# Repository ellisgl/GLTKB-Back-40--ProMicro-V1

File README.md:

# GLTKB Back 40% ProMicro V1
The other 40% mechanical keyboard.

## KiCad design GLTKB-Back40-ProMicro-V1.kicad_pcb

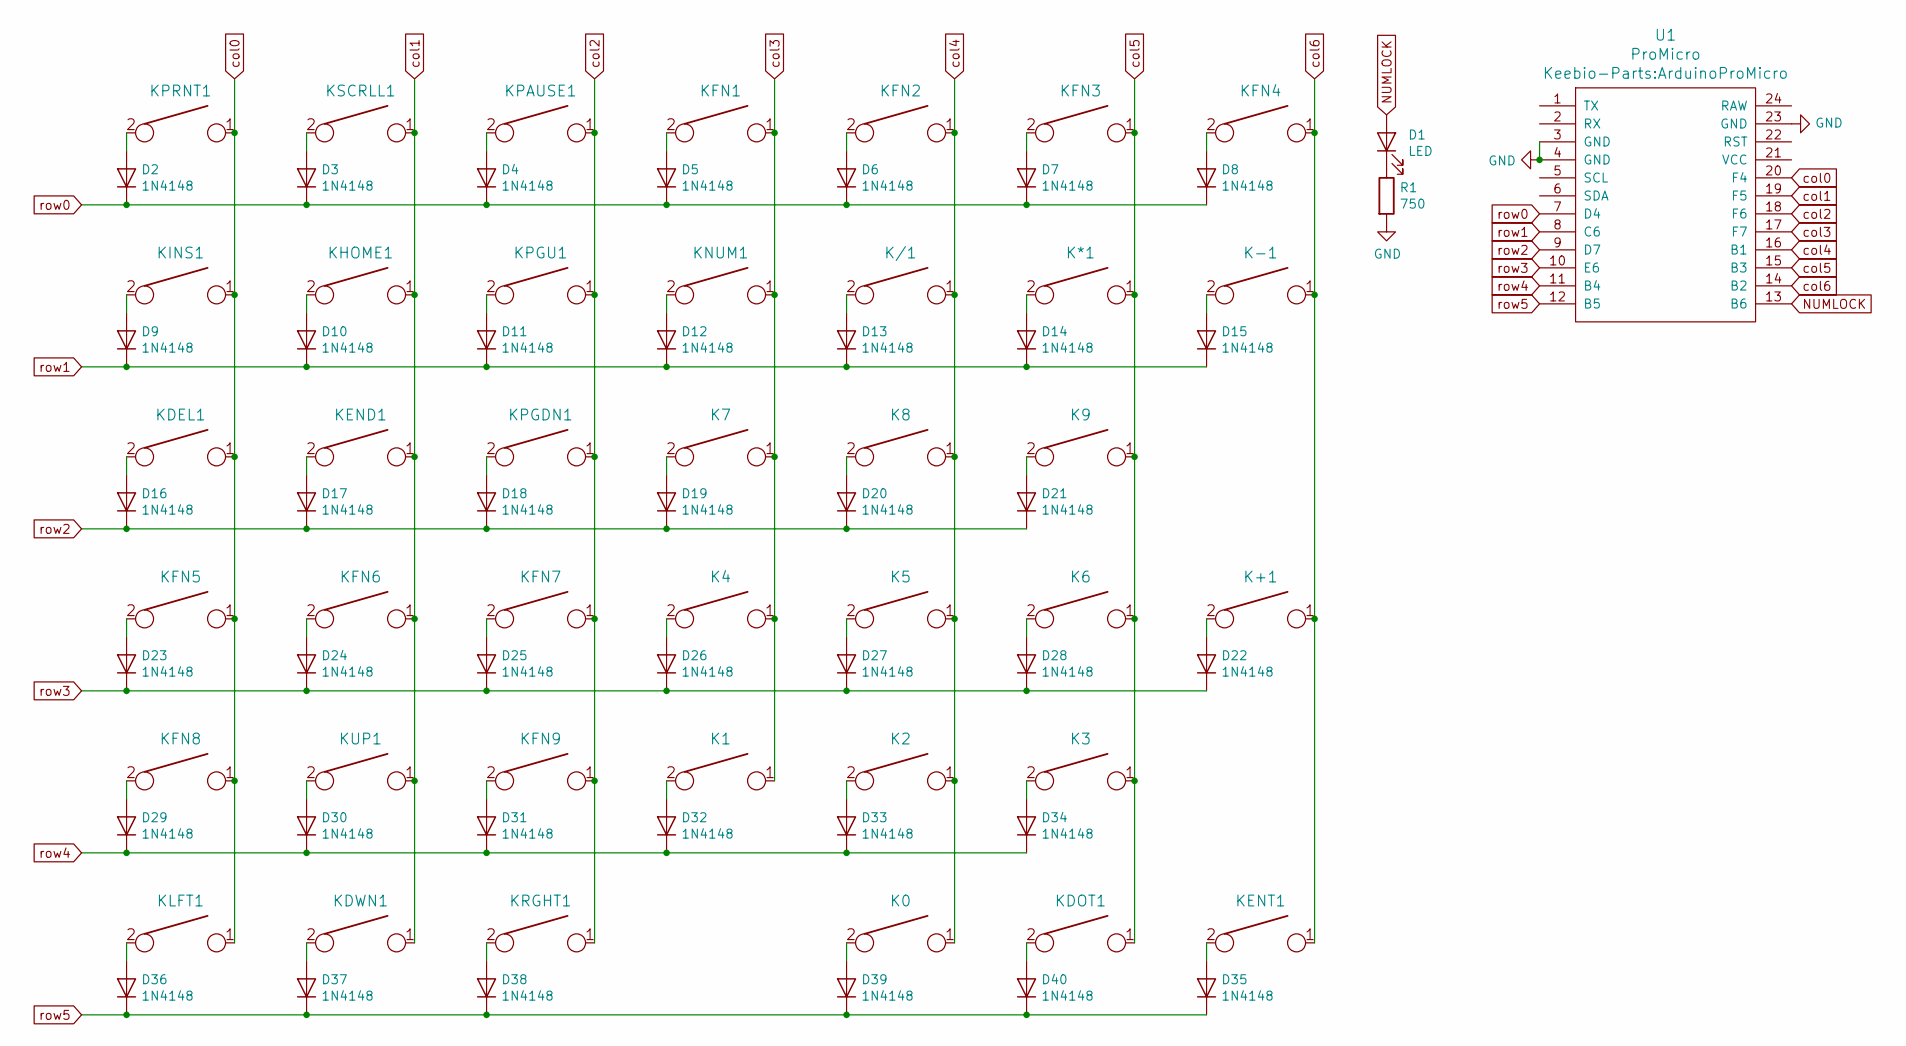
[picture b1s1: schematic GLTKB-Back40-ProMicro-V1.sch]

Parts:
D1: LED; LED_D3.0mm
D2, D3, D4, D5, D6, D7, D8, D9, D10, D11, D12, D13, D14, D15, D16, D17, D18, D19, D20, D21, D22, D23, D24, D25, D26, D27, D28, D29, D30, D31, D32, D33, D34, D35, D36, D37, D38, D39, D40: 1N4148; Diode-Hybrid-Back
K0, K1, K2, K3, K4, K5, K6, K7, K8, K9: KEYSW; Kailh_socket_MX
K*1: KEYSW; Kailh_socket_MX
K+1: KEYSW; Kailh_socket_MX
K-1: KEYSW; Kailh_socket_MX
K/1: KEYSW; Kailh_socket_MX
KDEL1: KEYSW; Kailh_socket_MX
KDOT1: KEYSW; Kailh_socket_MX
KDWN1: KEYSW; Kailh_socket_MX
KEND1: KEYSW; Kailh_socket_MX
KENT1: KEYSW; Kailh_socket_MX
KFN1, KFN2, KFN3, KFN4, KFN5, KFN6, KFN7, KFN8, KFN9: KEYSW; Kailh_socket_MX
KHOME1: KEYSW; Kailh_socket_MX
KINS1: KEYSW; Kailh_socket_MX
KLFT1: KEYSW; Kailh_socket_MX
KNUM1: KEYSW; Kailh_socket_MX
KPAUSE1: KEYSW; Kailh_socket_MX
KPGDN1: KEYSW; Kailh_socket_MX
KPGU1: KEYSW; Kailh_socket_MX
KPRNT1: KEYSW; Kailh_socket_MX
KRGHT1: KEYSW; Kailh_socket_MX
KSCRLL1: KEYSW; Kailh_socket_MX
KUP1: KEYSW; Kailh_socket_MX
R1: 750; R_Axial_DIN0207_L6.3mm_D2.5mm_P10.16mm_Horizontal
U1: ProMicro; ArduinoProMicro

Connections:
GND: R1.2, U1.3 (GND), U1.4 (GND), U1.23 (GND)
NUMLOCK: D1.2 (A), U1.13 (B6)
unnamed: D1.1 (K), R1.1
unnamed: D2.2 (A), KPRNT1.2
unnamed: D3.2 (A), KSCRLL1.2
unnamed: D4.2 (A), KPAUSE1.2
unnamed: D5.2 (A), KFN1.2
unnamed: D6.2 (A), KFN2.2
unnamed: D7.2 (A), KFN3.2
unnamed: D8.2 (A), KFN4.2
unnamed: D9.2 (A), KINS1.2
unnamed: D10.2 (A), KHOME1.2
unnamed: D11.2 (A), KPGU1.2
unnamed: D12.2 (A), KNUM1.2
unnamed: D13.2 (A), K/1.2
unnamed: D14.2 (A), K*1.2
unnamed: D15.2 (A), K-1.2
unnamed: D16.2 (A), KDEL1.2
unnamed: D17.2 (A), KEND1.2
unnamed: D18.2 (A), KPGDN1.2
unnamed: D19.2 (A), K7.2
unnamed: D20.2 (A), K8.2
unnamed: D21.2 (A), K9.2
unnamed: D22.2 (A), K+1.2
unnamed: D23.2 (A), KFN5.2
unnamed: D24.2 (A), KFN6.2
unnamed: D25.2 (A), KFN7.2
unnamed: D26.2 (A), K4.2
unnamed: D27.2 (A), K5.2
unnamed: D28.2 (A), K6.2
unnamed: D29.2 (A), KFN8.2
unnamed: D30.2 (A), KUP1.2
unnamed: D31.2 (A), KFN9.2
unnamed: D32.2 (A), K1.2
unnamed: D33.2 (A), K2.2
unnamed: D34.2 (A), K3.2
unnamed: D35.2 (A), KENT1.2
unnamed: D36.2 (A), KLFT1.2
unnamed: D37.2 (A), KDWN1.2
unnamed: D38.2 (A), KRGHT1.2
unnamed: D39.2 (A), K0.2
unnamed: D40.2 (A), KDOT1.2
col0: KDEL1.1, KFN5.1, KFN8.1, KINS1.1, KLFT1.1, KPRNT1.1, U1.20 (F4)
col1: KDWN1.1, KEND1.1, KFN6.1, KHOME1.1, KSCRLL1.1, KUP1.1, U1.19 (F5)
col2: KFN7.1, KFN9.1, KPAUSE1.1, KPGDN1.1, KPGU1.1, KRGHT1.1, U1.18 (F6)
col3: K1.1, K4.1, K7.1, KFN1.1, KNUM1.1, U1.17 (F7)
col4: K0.1, K2.1, K5.1, K8.1, K/1.1, KFN2.1, U1.16 (B1)
col5: K3.1, K6.1, K9.1, K*1.1, KDOT1.1, KFN3.1, U1.15 (B3)
col6: K+1.1, K-1.1, KENT1.1, KFN4.1, U1.14 (B2)
row0: D2.1 (K), D3.1 (K), D4.1 (K), D5.1 (K), D6.1 (K), D7.1 (K), D8.1 (K), U1.7 (D4)
row1: D9.1 (K), D10.1 (K), D11.1 (K), D12.1 (K), D13.1 (K), D14.1 (K), D15.1 (K), U1.8 (C6)
row2: D16.1 (K), D17.1 (K), D18.1 (K), D19.1 (K), D20.1 (K), D21.1 (K), U1.9 (D7)
row3: D22.1 (K), D23.1 (K), D24.1 (K), D25.1 (K), D26.1 (K), D27.1 (K), D28.1 (K), U1.10 (E6)
row4: D29.1 (K), D30.1 (K), D31.1 (K), D32.1 (K), D33.1 (K), D34.1 (K), U1.11 (B4)
row5: D35.1 (K), D36.1 (K), D37.1 (K), D38.1 (K), D39.1 (K), D40.1 (K), U1.12 (B5)

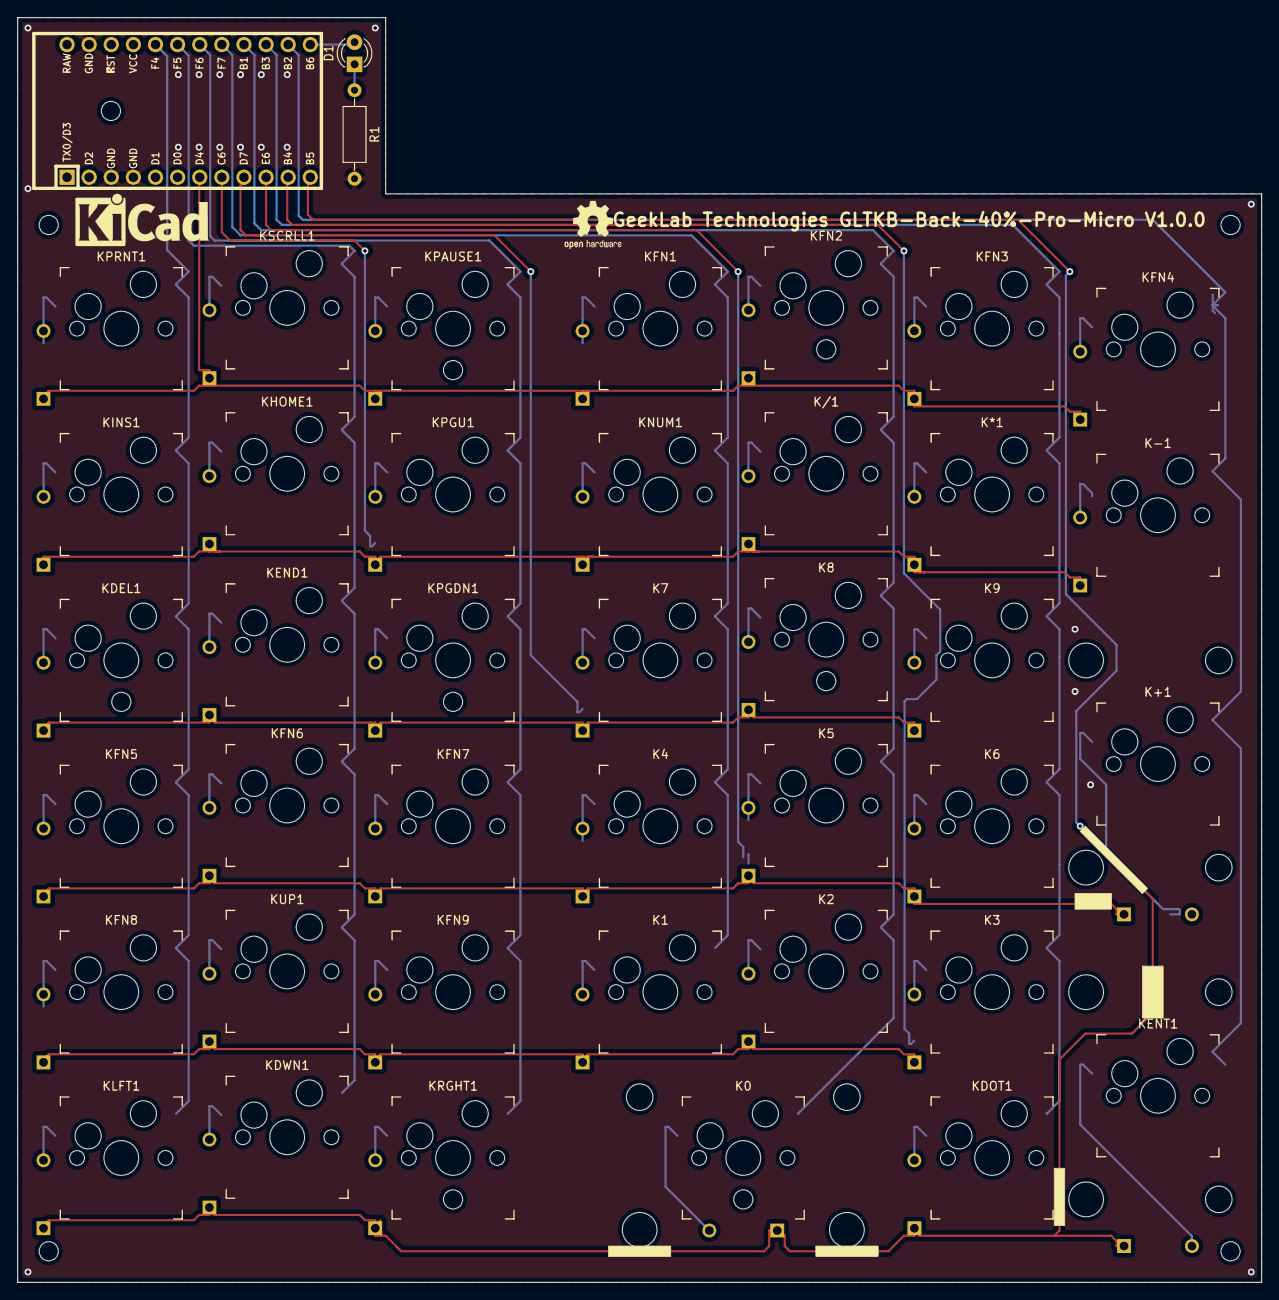
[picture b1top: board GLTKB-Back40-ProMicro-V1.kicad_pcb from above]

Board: 2 copper layers, 142.9 x 145.3 mm, 81 parts (0 on the bottom side), 55 nets.

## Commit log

2020-03-14 Initial.
2020-03-14 Removed uneeded front silk trace protector, since it wasn't protecting a front side trace.
2020-03-14 Fixing a punctuation error, period.
2020-03-14 Move some mounting holes.
2020-03-15 Tweaking track to pad connections.
